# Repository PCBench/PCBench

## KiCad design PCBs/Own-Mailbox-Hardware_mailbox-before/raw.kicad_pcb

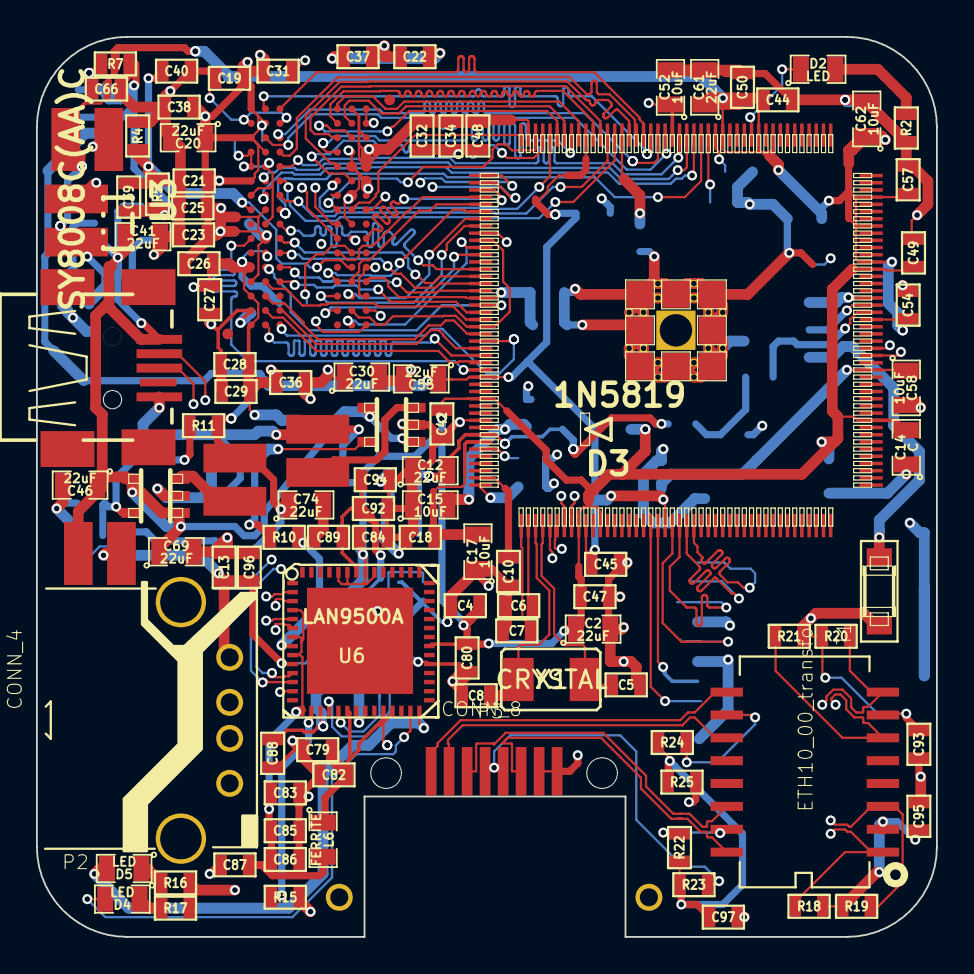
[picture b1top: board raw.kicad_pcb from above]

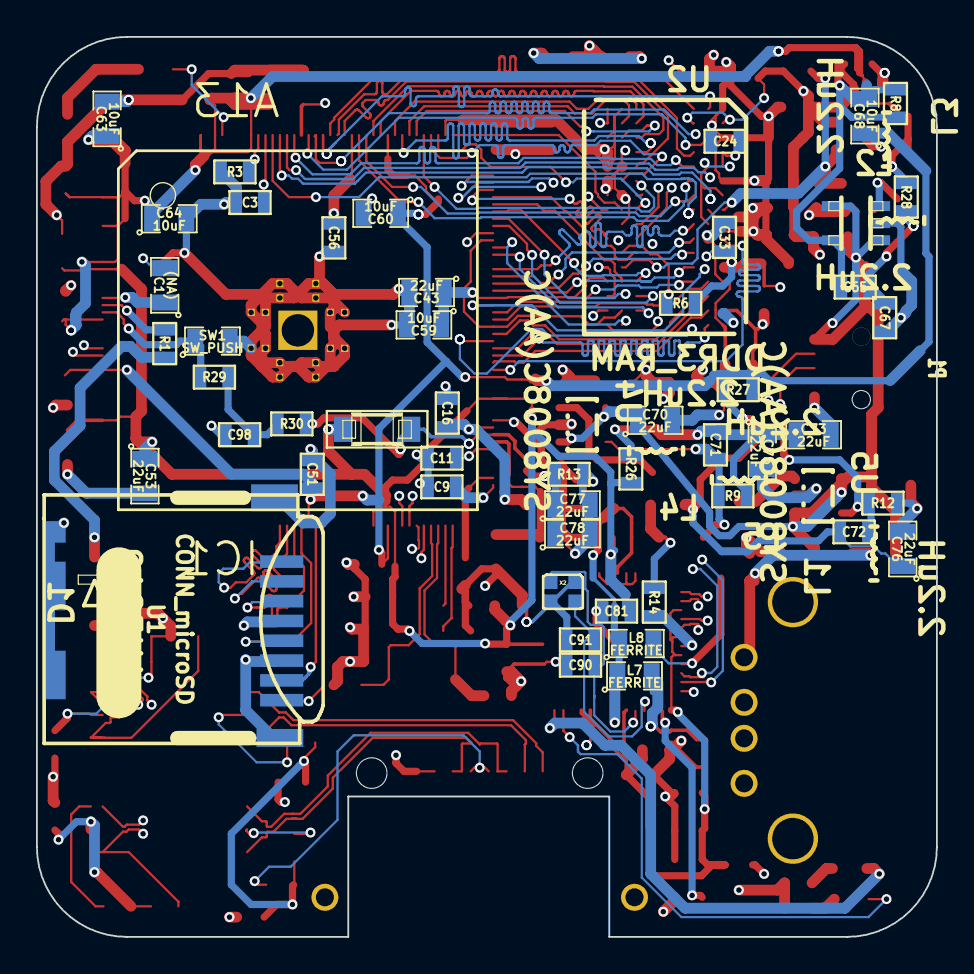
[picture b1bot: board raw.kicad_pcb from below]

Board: 4 copper layers, 50.0 x 50.0 mm, 154 parts (50 on the bottom side), 74 nets.

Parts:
C1: (NA); SM0805
C2, C12, C20, C30, C41, C43, C46, C53, C55, C61, C69, C70, C73, C74, C75, C76, C77, C78: 22uF; SM0805
C3, C4, C13, C16, C18, C19, C21, C23, C24, C25, C26, C27, C28, C29, C31, C32, C33, C34, C36, C37, C38, C39, C40, C42, C44, C45, C47, C48, C49, C50, C51, C54, C56, C57, C79, C80, C81, C82, C83, C84, C85, C86, C87, C88, C92, C93, C94, C95, C96: 100nF; SM0603
C5, C8, C90, C91: 10pF; SM0603
C6, C7, C9, C10, C22, C98: 1nF; SM0603
C11, C89, C97: 1uF; SM0603
C14: C; SM0805
C15, C17, C52, C58, C59, C60, C62, C63, C64, C68: 10uF; SM0805
C65, C72: 22pF; SM0603
C66, C67: 22uF; SM0603
C71: 47pF; SM0603
D1, D3: 1N5819; SOD-123
D2, D4, D5: LED; SM0805
IC1: A13; TQFP176
L1, L2, L3, L4, L5: 2.2uH; CD32
L6, L7, L8: FERRITE; SM0805
P1: CONN_4; CONN_USB_MINI_PIERRE
P2: CONN_4; USB-A_TH
P3: CONN_8; RJ45_LP_RA_SMT
R1: 47k; SM0603
R2: 500R; SM0603
R3: 240R; SM0603
R4, R5: 1k(1%); SM0603
R6: 240R(1%); SM0603
R7: 2k(1%); SM0603
R8: 1.5k(1%); SM0603
R9: 100k(1%); SM0603
R10: 22k(1%); SM0603
R11: 4.99k(1%); SM0603
R12: 3.3k(1%); SM0603
R13: 2.2k; SM0603
R14, R15: R; SM0603
R16, R17: 100R; SM0603
R18, R19, R20, R21: 50R; SM0603
R22, R23, R24, R25: 75R; SM0603
R26, R27, R28: 0R; SM0603
R29: 6.8k(1%); SM0603
R30: 100k (1%); SM0603
SW1: SW_PUSH; SM0805
T1: ETH10_00_transfo; H1601CG
U1: CONN_microSD; Memory_Card_microSD_DM3CS-SF
U2: DDR3_RAM; FBGA96
U3, U4, U5: SY8008C(AA)C; SOT23-5
U6: LAN9500A; QFN48
X1: CRYSTAL; SMDXTAL24mhz
X2: CRYSTAL_SMD2; Xtal25Mhz

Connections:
1V5: C19.1, C20.1, C21.1, C23.1, C24.1, C25.1, C26.1, C27.1, C28.1, C29.1, C30.1, C31.1, C32.1, C33.1, C34.1, C36.1, C37.1, C38.1, C39.1, C43.1, C48.1, C52.1, C56.1, C59.1, IC1.23, IC1.30, IC1.43, IC1.53, IC1.62, R5.1, R27.1, U2.A1, U2.A8, U2.B2, U2.C1, U2.C9, U2.D2, U2.D9, U2.E9, U2.F1, U2.G7, U2.H2, U2.H9, U2.K2, U2.K8, U2.N1, U2.N9, U2.R1, U2.R9
3VA: C12.2, C77.1, C78.1, D3.2, IC1.81, R13.1, R30.1
+5V: C41.1, C46.1, C69.1, C70.1, L1.2, P1.1, U3.1, U3.4, U4.1, U4.4, U5.1, U5.4
/Erhernet/RX+: P3.7, T1.11
/Erhernet/RX-: P3.8, T1.9
/Erhernet/TX+: P3.3, T1.16
/Erhernet/TX-: P3.6, T1.14
LED1: D4.2, U6.27
LED2: D5.2, U6.28
unnamed: C1.1, IC1.159
unnamed: C3.1, IC1.18
unnamed: C6.2, IC1.90
unnamed: C7.2, IC1.89
unnamed: C9.2, IC1.88
unnamed: C10.2, IC1.87
unnamed: C11.2, IC1.83
unnamed: C13.1, L1.1, P2.1
unnamed: C15.2, C16.2, IC1.80
unnamed: C17.2, C18.2, IC1.82
unnamed: C22.2, IC1.86
unnamed: C39.2, C40.1, R4.1, R5.2, U2.H1, U2.M8
unnamed: C65.1, C66.1, C67.1, L2.2, R7.1, R28.2
unnamed: C71.1, C73.1, C75.1, L4.2, R9.1, R26.2
unnamed: C71.2, R9.2, R10.1, U4.5
unnamed: C72.1, C74.1, C76.1, L5.2, R11.1, R27.2
unnamed: C72.2, R11.2, R12.1, U5.5
unnamed: C90.2, U6.19, X2.3
unnamed: C91.2, U6.18, X2.1
unnamed: C97.2, R22.1, R23.1, R24.1, R25.1
unnamed: C98.1, R29.1, R30.2
unnamed: D1.2, R1.1
unnamed: D2.1, IC1.12
unnamed: D2.2, R2.1
unnamed: D4.1, R17.1
unnamed: D5.1, R16.1
unnamed: IC1.17, R3.1
unnamed: IC1.158, R1.2
unnamed: L2.1, U3.3
unnamed: L4.1, U4.3
unnamed: L5.1, U5.3
unnamed: P3.1, P3.2, R25.2
unnamed: P3.4, P3.5, R23.2
unnamed: R6.1, U2.L8
unnamed: R14.2, U6.8
unnamed: R15.2, U6.16
unnamed: R22.2, T1.15
unnamed: R24.2, T1.10
RPX_N: R20.1, T1.8, U6.5
RPX_P: R21.1, T1.6, U6.6
SDC0_CLK: IC1.110, U1.5
SDC0_CMD: IC1.111, U1.3
SDC0_D0: IC1.108, U1.7
SDC0_D1: IC1.107, U1.8
SDC0_D2: IC1.113, U1.1
SDC0_D3: IC1.112, U1.2
SVREF: C1.2, C2.2, C3.2, C4.1, C5.1, C6.1, C7.1, C8.1, C9.1, C10.1, C11.1, C12.1, C13.2, C14.1, C15.1, C16.1, C17.1, C18.1, C19.2, C20.2, C21.2, C22.1, C23.2, C24.2, C25.2, C26.2, C27.2, C28.2, C29.2, C30.2, C31.2, C32.2, C33.2, C34.2, C36.2, C37.2, C38.2, C40.2, C41.2, C42.2, C43.2, C44.2, C45.2, C46.2, C47.2, C48.2, C49.2, C50.2, C51.2, C52.2, C53.2, C54.2, C55.2, C56.2, C57.2, C58.2, C59.2, C60.2, C61.2, C62.2, C63.2, C64.2, C65.2, C66.2, C67.2, C68.2, C69.2, C70.2, C73.2, C74.2, C75.2, C76.2, C77.2, C78.2, C79.2, C80.2, C81.2, C82.2, C83.2, C84.2, C85.2, C86.2, C87.2, C88.2, C89.2, C90.1, C91.1, C92.2, C93.1, C94.2, C95.2, C96.2, C97.1, C98.2, IC1.79, IC1.177, P1.4, P2.4, R2.2, R3.2, R4.2, R6.2, R7.2, R8.1, R8.2, R10.2, R12.2, R13.2, R14.1, R15.1, SW1.2, U1.6, U1.9, U2.A9, U2.B1, U2.B3, U2.B9, U2.D1, U2.D8, U2.E1, U2.E2, U2.E8, U2.F9, U2.G1, U2.G8, U2.G9, U2.J2, U2.J8, U2.L2, U2.M1, U2.M9, U2.P1, U2.P9, U2.T1, U2.T9, U3.2, U3.5, U4.2, U5.2, U6.13, U6.33, X2.2, X2.4
TPX_N: R19.2, T1.3, U6.2
TPX_P: R18.2, T1.1, U6.3
UART1_RX: IC1.151, P1.3
UART1_TX: IC1.152, P1.2
UBOOT: IC1.157, R29.2, SW1.1
USB_ETH_N: IC1.93, U6.11
USB_ETH_P: IC1.94, U6.12
USB_HOST_N: IC1.95, P2.2
USB_HOST_P: IC1.96, P2.3
VCC: C2.1, C4.2, C14.2, C42.1, C47.1, C49.1, C53.1, C79.1, C80.1, C81.1, C82.1, C84.1, C93.2, C95.1, D1.1, D3.1, IC1.5, IC1.76, IC1.97, IC1.100, IC1.142, IC1.163, L6.1, R16.2, R17.2, R18.1, R19.1, R20.2, R21.2, R26.1, T1.2, T1.7, U1.4, U6.20, U6.24, U6.25, U6.35, U6.48, U6.49, U6.51, U6.52
VDD33A: C83.1, C85.1, C86.1, C87.1, L6.2, U6.4, U6.7, U6.9, U6.15
VDDBUSPLL: C88.1, L7.2, U6.17
VDDCORE: C89.1, C92.1, C94.1, L7.1, L8.1, U6.21, U6.50
VDDPLL: C96.1, L8.2, U6.10
VDD_CPU: C44.1, C50.1, C54.1, C57.1, C61.1, C62.1, C63.1, C64.1, IC1.4, IC1.9, IC1.11, IC1.16, IC1.156, IC1.164, IC1.169, IC1.173, L3.1, R28.1
VDD_INT: C45.1, C51.1, C55.1, C58.1, C60.1, C68.1, IC1.35, IC1.73, IC1.98, IC1.109, IC1.149, L3.2
X1_N: C5.2, IC1.92, X1.1
X1_P: C8.2, IC1.91, X1.2

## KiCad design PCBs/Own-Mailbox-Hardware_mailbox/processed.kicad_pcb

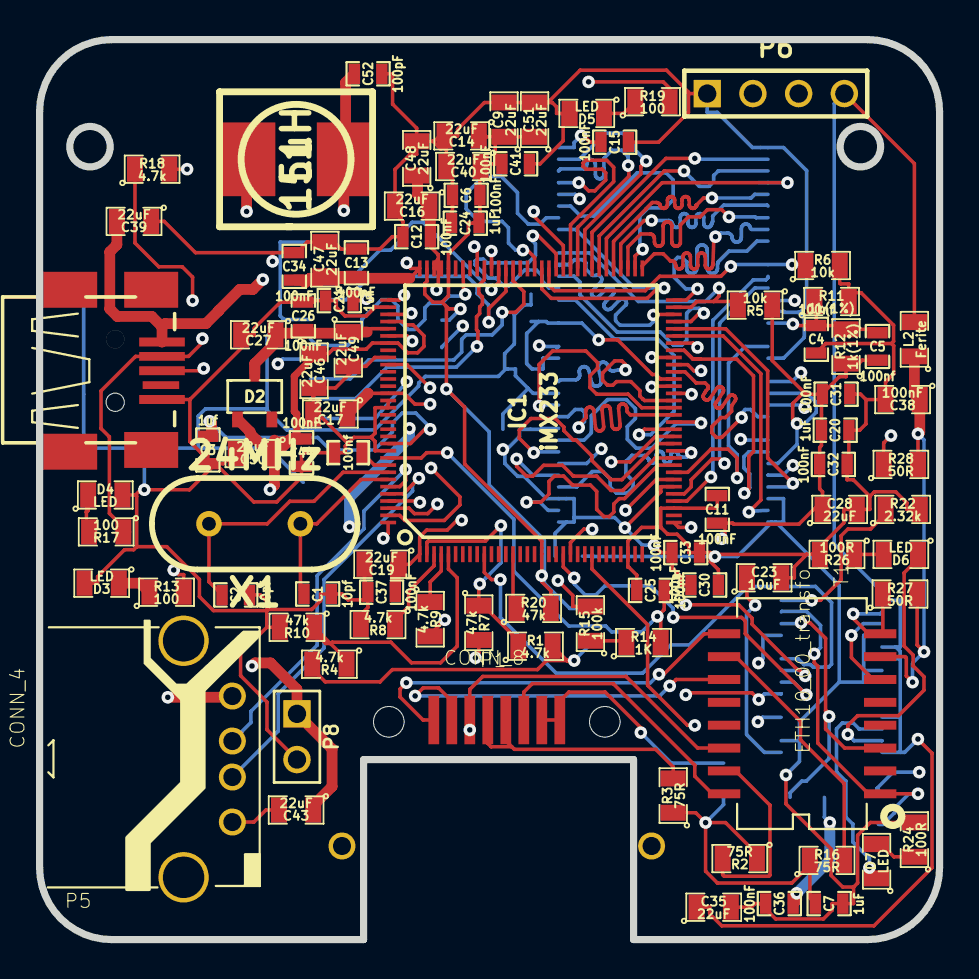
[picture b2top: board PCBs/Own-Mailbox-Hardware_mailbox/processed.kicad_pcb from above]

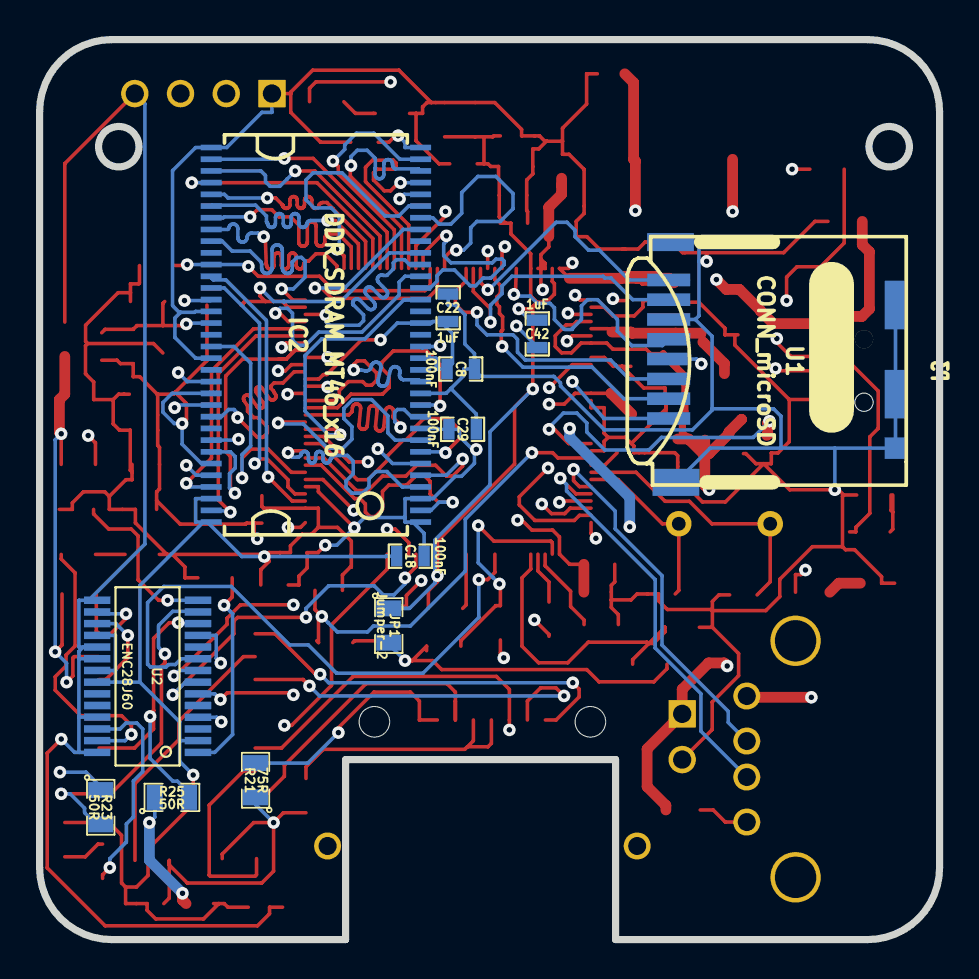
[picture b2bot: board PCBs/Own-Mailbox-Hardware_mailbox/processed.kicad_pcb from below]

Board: 4 copper layers, 50.0 x 50.0 mm, 99 parts (12 on the bottom side), 107 nets.

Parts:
C1, C2: 10pf; SM0603_Capa
C3: 1uf; SM0603_Capa
C4, C5: 100nf; SM0603_Capa
C6, C8, C11, C12, C13, C15, C18, C25, C26, C29, C30, C31, C32, C33, C34, C36, C37, C41, C44: 100nF; SM0603_Capa
C7, C20, C21, C22, C24, C42: 1uF; SM0603_Capa
C9, C14, C16, C17, C19, C27, C28, C35, C39, C40, C43, C46, C47, C48, C49, C50, C51: 22uF; SM0805
C10: 100nf; SM0603_Opendous
C23: 10uF; SM0805
C38: 100nF; SM0805
C52: 100pF; SM0603_Capa
D2: D_schottky; SOT23-3_Opendous
D3, D4, D5, D6, D7: LED; SM0805
IC1: iMX233; LQFP128_14x14mm_0.4mmPitch_iMX233
IC2: DDR_SDRAM_MT46_x16; TSOP66_JEDEC_DDR_SDRAM
JP1: Jumper-2; SM0805
L1: 15uH; inductor22
L2: Ferite; SM0805
P1: CONN_8; RJ45_LP_RA_SMT
P3: CONN_4; CONN_USB_MINI_PIERRE
P5: CONN_4; USB-A_TH
P6: CONN_4; PIN_ARRAY_4x1
P8: CONN_2; PIN_ARRAY_2X1
R1, R4, R8, R9, R18: 4.7k; SM0805
R2, R3, R16, R21: 75R; SM0805
R5, R6: 10k; SM0805
R7, R10, R20: 47k; SM0805
R11, R12: 1k(1%); SM0805
R13, R17, R19: 100; SM0805
R14: 1K; SM0805
R15: 100k; SM0805
R22: 2.32k; SM0805
R23, R25, R27, R28: 50R; SM0805
R24, R26: 100R; SM0805
T1: ETH10_00_transfo; H1601CG
U1: CONN_microSD; Memory_Card_microSD_DM3CS-SF
U2: ENC28J60; tssop-28
X1: 24MHz; HC-49V

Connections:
5VOUT: C21.1, C39.2, IC1.102, P3.1, P5.1
+2.5V: C5.1, C8.1, C11.1, C15.1, C18.1, C20.1, C22.1, C28.1, C29.1, C30.1, C31.1, C32.1, C33.1, IC1.38, IC1.45, IC1.53, IC1.106, IC2.1, IC2.3, IC2.9, IC2.15, IC2.18, IC2.33, IC2.55, IC2.61, R5.1, R12.1
+3.3V: C6.1, C9.1, C14.1, C24.1, C35.1, C40.1, C41.1, C42.1, C51.1, IC1.18, IC1.92, IC1.95, JP1.1, L2.2, P6.4, R13.2, R18.2, R20.2, U1.4, U2.15, U2.19, U2.20, U2.25, U2.28
/Ethernet/RX+: P1.7, T1.11
/Ethernet/RX-: P1.8, T1.9
/Ethernet/TX+: P1.3, T1.16
/Ethernet/TX-: P1.6, T1.14
/LCD_D0: IC1.2, R1.1, R7.1
/LCD_D1: IC1.3, R8.1
/LCD_D2: IC1.4, R9.1
/LCD_D3: IC1.5, R4.1, R10.1
/LCD_RS: IC1.14, R20.1
/SD_CLOCK: IC1.90, U1.5
/SD_CMD: IC1.83, U1.3
/UART2_RX: IC1.128, P6.3
/UART2_TX: IC1.127, P6.2
/U_RX: IC1.125, P3.3, R18.1
/U_TX: IC1.126, P3.2, R17.1
DDRA0: IC1.76, IC2.29
DDRA1: IC1.75, IC2.30
DDRA2: IC1.74, IC2.31
DDRA3: IC1.73, IC2.32
DDRA4: IC1.72, IC2.35
DDRA5: IC1.71, IC2.36
DDRA6: IC1.70, IC2.37
DDRA7: IC1.69, IC2.38
DDRA8: IC1.68, IC2.39
DDRA9: IC1.67, IC2.40
DDRA10: IC1.66, IC2.28
DDRA11: IC1.65, IC2.41
DDRA12: IC1.64, IC2.42
DDR_BA0: IC1.79, IC2.26
DDR_BA1: IC1.80, IC2.27
DDR_CAS: IC1.61, IC2.22
DDR_CE0n: IC1.63, IC2.24, R5.2
DDR_CKE: IC1.78, IC2.44, R6.1
DDR_CLK: IC1.36, IC2.45
DDR_CLKn: IC1.37, IC2.46
DDR_DO0: IC1.41, IC2.2
DDR_DO1: IC1.43, IC2.4
DDR_DO2: IC1.42, IC2.5
DDR_DO3: IC1.44, IC2.7
DDR_DO4: IC1.47, IC2.8
DDR_DO5: IC1.48, IC2.10
DDR_DO6: IC1.49, IC2.11
DDR_DO7: IC1.50, IC2.13
DDR_DO8: IC1.51, IC2.54
DDR_DO9: IC1.52, IC2.56
DDR_DO10: IC1.54, IC2.57
DDR_DO11: IC1.55, IC2.59
DDR_DO12: IC1.57, IC2.60
DDR_DO13: IC1.58, IC2.62
DDR_DO14: IC1.60, IC2.63
DDR_DO15: IC1.59, IC2.65
DDR_DQM0: IC1.46, IC2.20
DDR_DQM1: IC1.56, IC2.47
DDR_DQS0: IC1.39, IC2.16
DDR_DQS1: IC1.40, IC2.51
DDR_RAS: IC1.62, IC2.23
DDR_WEn: IC1.77, IC2.21
GND: C1.1, C2.1, C3.2, C4.2, C6.2, C7.1, C8.2, C9.2, C10.2, C11.2, C12.2, C13.2, C14.2, C15.2, C16.2, C17.2, C18.2, C19.2, C20.2, C21.2, C22.2, C23.2, C24.2, C25.2, C26.2, C27.2, C28.2, C29.2, C30.2, C31.2, C32.2, C33.2, C34.2, C35.2, C36.1, C37.2, C38.2, C39.1, C40.2, C41.2, C42.2, C43.2, C44.2, C46.2, C47.2, C48.2, C49.2, C50.2, C51.2, C52.1, D3.2, D4.2, D5.2, IC1.30, IC1.35, IC1.98, IC1.105, IC1.111, IC1.112, IC1.118, IC2.6, IC2.12, IC2.34, IC2.48, IC2.52, IC2.64, IC2.66, P3.4, P5.4, P6.1, P8.2, R6.2, R7.2, R8.2, R9.2, R10.2, R11.2, R15.2, R22.2, R24.2, R26.2, U1.6, U1.9, U2.2, U2.11, U2.18, U2.21, U2.22
unnamed: C3.1, IC1.117
unnamed: C4.1, C5.2, IC2.49, R11.1, R12.2
unnamed: C7.2, R2.1, R3.1, R16.1, R21.1
unnamed: C23.1, U2.1
unnamed: C36.2, R23.1, R25.1
unnamed: C38.1, L2.1, R27.2, R28.2, T1.7
unnamed: C52.2, IC1.99, L1.2
unnamed: D3.1, R13.1
unnamed: D4.1, R17.2
unnamed: D5.1, R19.1
unnamed: D6.1, U2.27
unnamed: D6.2, R26.1
unnamed: D7.1, U2.26
unnamed: D7.2, R24.1
unnamed: IC1.84, U1.7
unnamed: IC1.85, U1.8
unnamed: IC1.86, U1.1
unnamed: IC1.87, U1.2
unnamed: IC1.88, R19.2
unnamed: IC1.97, L1.1
unnamed: IC1.123, P5.2
unnamed: IC1.124, P5.3
unnamed: JP1.2, R1.2, R4.2
unnamed: P1.1, P1.2, R21.2
unnamed: P1.4, P1.5, R3.2
unnamed: R2.2, T1.15
unnamed: R14.1, R15.1
unnamed: R16.2, T1.10
unnamed: R22.1, U2.14
unnamed: R23.2, T1.1, U2.13
unnamed: R25.2, T1.3, U2.12
unnamed: R27.1, T1.8, U2.16
unnamed: R28.1, T1.6, U2.17
PSWITCH: C25.1, IC1.119, R14.2
SPI_CS: IC1.10, U2.9
SPI_INT: IC1.25, U2.4
SPI_MISO: IC1.22, U2.6
SPI_MOSI: IC1.21, U2.7
SPI_SCK: IC1.33, U2.8
VDD4P2: C26.1, C27.1, C49.1, D2.2, IC1.101
VDDA: C13.1, C17.1, C34.1, C47.1, IC1.96, IC1.110
VDDD: C12.1, C16.1, C19.1, C37.1, C48.1, IC1.1, IC1.93, IC1.94
VDD_BATT: C43.1, C44.1, C46.1, C50.1, D2.1, IC1.100, IC1.103, P8.1
VDD_XTAL: C10.1, IC1.120
XTALI: C1.2, IC1.122, X1.1
XTALO: C2.2, IC1.121, X1.2

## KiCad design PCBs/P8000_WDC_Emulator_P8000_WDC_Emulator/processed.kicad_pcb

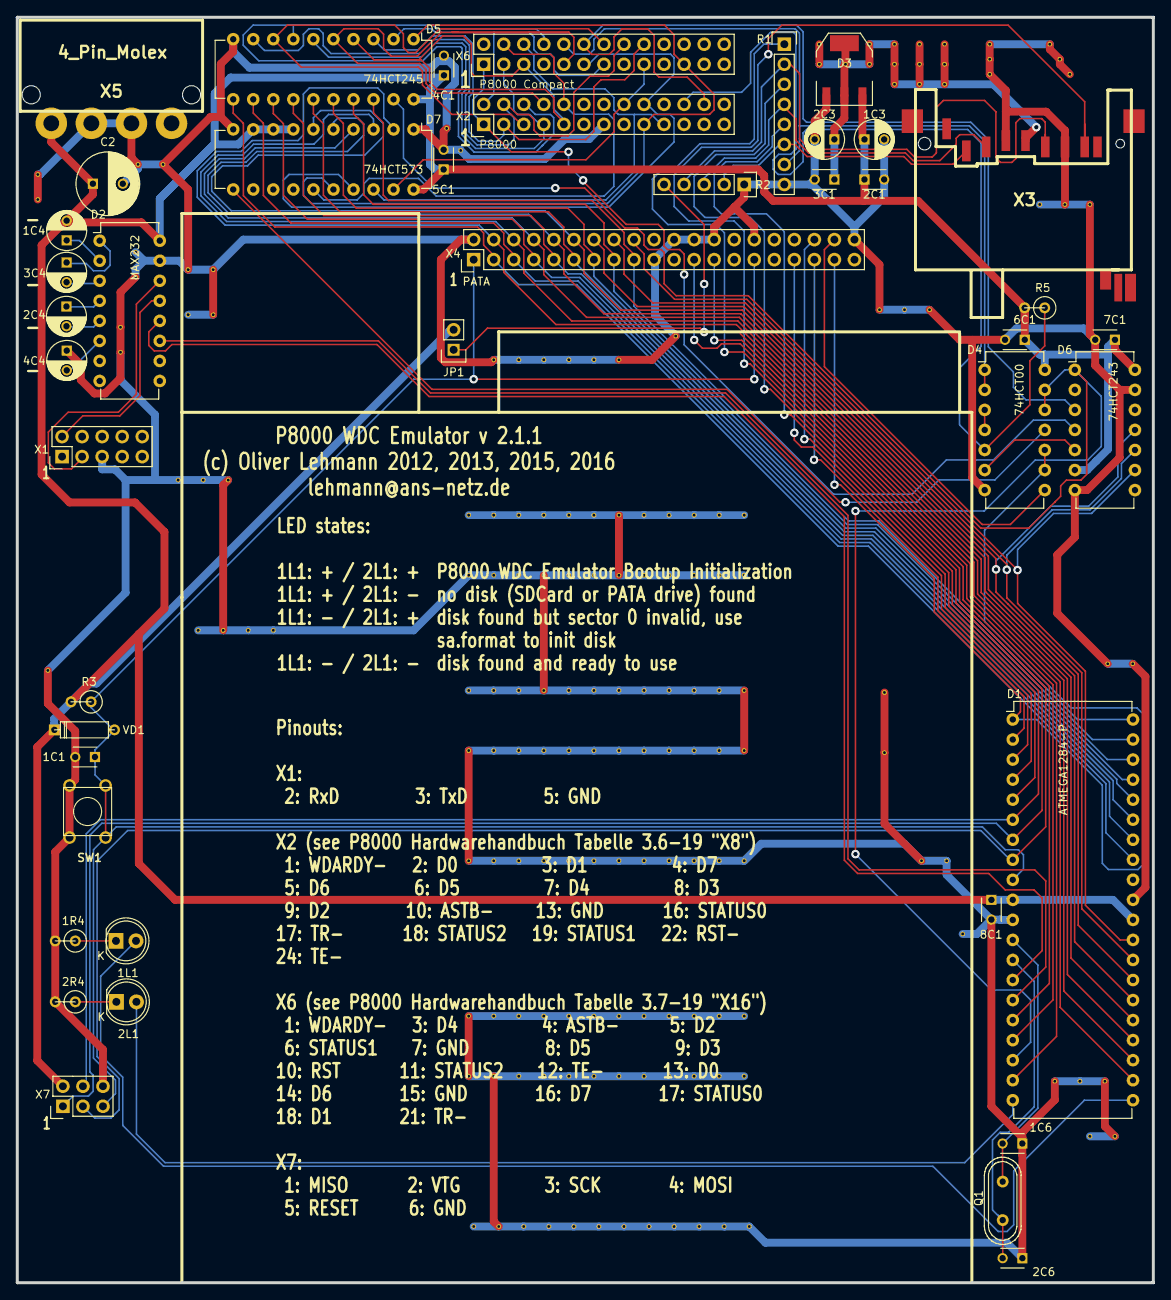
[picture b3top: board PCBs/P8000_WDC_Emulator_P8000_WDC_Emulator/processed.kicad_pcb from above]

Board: 2 copper layers, 144.0 x 160.4 mm, 214 parts (0 on the bottom side), 72 nets.

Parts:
1C1, 2C1, 3C1, 4C1, 5C1, 6C1, 7C1, 8C1: 100n; C_Disc_D3_P2.5
1C3, 2C3: 100u; C_Radial_D5_L6_P2.5
1C4, 2C4, 3C4, 4C4: 1u; C_Radial_D5_L6_P2.5
1C6, 2C6: 22p; C_Disc_D3_P2.5
1L1, 2L1: LED; LED-5MM
1R4, 2R4: 300; R1
C2: 470u; C_Radial_D8_L13_P3.8
D1: ATMEGA1284-P; DIP-40_W15.24mm
D2: MAX232; DIP-16_W7.62mm
D3: TS1117 BCW33; SOT-223
D4: 74HCT00; DIP-14_W7.62mm
D5: 74HCT245; DIP-20_W7.62mm
D6: 74HCT243; DIP-14_W7.62mm
D7: 74HCT573; DIP-20_W7.62mm
Hole-Inner-1, Hole-Inner-2, Hole-Inner-3, Hole-Inner-4: VAL**; HOLE_4x8mm_4mmclear_pad
Hole-Outer-1, Hole-Outer-2, Hole-Outer-3, Hole-Outer-4: VAL**; HOLE_4x8mm_pad
JP1: JUMPER; Pin_Header_Straight_1x02
Q1: CRYSTAL; Crystal_HC49-U_Vertical
R1: 1k8; Pin_Header_Straight_1x08
R2: 3k3; Pin_Header_Straight_1x05
R3: 10k; R1
R5: 4k7; R1
SW1: SW_PUSH; SW_6x6
VD1: 1N4148; D3
VIA-0.6mm, VIA-0.6mm_2, VIA-0.6mm_3, VIA-0.6mm_4, VIA-0.6mm_5, VIA-0.6mm_6, VIA-0.6mm_7, VIA-0.6mm_8, VIA-0.6mm_9, VIA-0.6mm_10, VIA-0.6mm_11, VIA-0.6mm_12, VIA-0.6mm_13, VIA-0.6mm_14, VIA-0.6mm_15, VIA-0.6mm_16, VIA-0.6mm_17, VIA-0.6mm_18, VIA-0.6mm_19, VIA-0.6mm_20, VIA-0.6mm_21, VIA-0.6mm_22, VIA-0.6mm_23, VIA-0.6mm_24, VIA-0.6mm_25, VIA-0.6mm_26, VIA-0.6mm_27, VIA-0.6mm_28, VIA-0.6mm_29, VIA-0.6mm_30, VIA-0.6mm_31, VIA-0.6mm_32, VIA-0.6mm_33, VIA-0.6mm_34, VIA-0.6mm_35, VIA-0.6mm_36, VIA-0.6mm_37, VIA-0.6mm_38, VIA-0.6mm_39, VIA-0.6mm_40, VIA-0.6mm_41, VIA-0.6mm_42, VIA-0.6mm_43, VIA-0.6mm_44, VIA-0.6mm_45, VIA-0.6mm_46, VIA-0.6mm_47, VIA-0.6mm_48, VIA-0.6mm_49, VIA-0.6mm_50, VIA-0.6mm_51, VIA-0.6mm_52, VIA-0.6mm_53, VIA-0.6mm_54, VIA-0.6mm_55, VIA-0.6mm_56, VIA-0.6mm_57, VIA-0.6mm_58, VIA-0.6mm_59, VIA-0.6mm_60, VIA-0.6mm_61, VIA-0.6mm_62, VIA-0.6mm_63, VIA-0.6mm_64, VIA-0.6mm_65, VIA-0.6mm_66, VIA-0.6mm_67, VIA-0.6mm_68, VIA-0.6mm_69, VIA-0.6mm_70, VIA-0.6mm_71, VIA-0.6mm_72, VIA-0.6mm_73, VIA-0.6mm_74, VIA-0.6mm_75, VIA-0.6mm_76, VIA-0.6mm_77, VIA-0.6mm_78, VIA-0.6mm_79, VIA-0.6mm_80, VIA-0.6mm_81, VIA-0.6mm_82, VIA-0.6mm_83, VIA-0.6mm_84, VIA-0.6mm_85, VIA-0.6mm_86, VIA-0.6mm_87, VIA-0.6mm_88, VIA-0.6mm_89, VIA-0.6mm_90, VIA-0.6mm_91, VIA-0.6mm_92, VIA-0.6mm_93, VIA-0.6mm_94, VIA-0.6mm_95, VIA-0.6mm_96, VIA-0.6mm_97, VIA-0.6mm_98, VIA-0.6mm_99, VIA-0.6mm_100, VIA-0.6mm_101, VIA-0.6mm_102, VIA-0.6mm_103, VIA-0.6mm_104, VIA-0.6mm_105, VIA-0.6mm_106, VIA-0.6mm_107, VIA-0.6mm_108, VIA-0.6mm_109, VIA-0.6mm_110, VIA-0.6mm_111, VIA-0.6mm_112, VIA-0.6mm_113, VIA-0.6mm_114, VIA-0.6mm_115, VIA-0.6mm_116, VIA-0.6mm_117, VIA-0.6mm_118, VIA-0.6mm_119, VIA-0.6mm_120, VIA-0.6mm_121, VIA-0.6mm_122, VIA-0.6mm_123, VIA-0.6mm_124, VIA-0.6mm_125, VIA-0.6mm_126, VIA-0.6mm_127, VIA-0.6mm_128, VIA-0.6mm_129, VIA-0.6mm_130, VIA-0.6mm_131, VIA-0.6mm_132, VIA-0.6mm_133, VIA-0.6mm_134, VIA-0.6mm_135, VIA-0.6mm_136, VIA-0.6mm_137, VIA-0.6mm_138, VIA-0.6mm_139, VIA-0.6mm_140, VIA-0.6mm_141, VIA-0.6mm_142, VIA-0.6mm_143, VIA-0.6mm_144, VIA-0.6mm_145, VIA-0.6mm_146, VIA-0.6mm_147, VIA-0.6mm_148, VIA-0.6mm_149, VIA-0.6mm_150, VIA-0.6mm_151, VIA-0.6mm_152, VIA-0.6mm_153, VIA-0.6mm_154, VIA-0.6mm_155, VIA-0.6mm_156, VIA-0.6mm_157, VIA-0.6mm_158, VIA-0.6mm_159, VIA-0.6mm_160, VIA-0.6mm_161, VIA-0.6mm_162, VIA-0.6mm_163: VAL**; VIA-0.6mm
X1: RS-232; Pin_Header_Straight_2x05
X2: P8000; Pin_Header_Straight_2x13
X3: SD-CON; sd_cocket_yamaichi_fps009_3001
X4: PATA; Pin_Header_Straight_2x20
X5: 4_Pin_Molex; 4PIN_MOLEX
X6: P8000-Compact; Pin_Header_Straight_2x13
X7: AVR-ISP-6; Pin_Header_Straight_2x03

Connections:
+3V3: 2C3.1, 3C1.1, D3.2, VIA-0.6mm_117.1, VIA-0.6mm_118.1, VIA-0.6mm_119.1, VIA-0.6mm_120.1, VIA-0.6mm_121.1, VIA-0.6mm_122.1, VIA-0.6mm_123.1, VIA-0.6mm_124.1, VIA-0.6mm_125.1, VIA-0.6mm_126.1, VIA-0.6mm_127.1, VIA-0.6mm_128.1, VIA-0.6mm_129.1, VIA-0.6mm_130.1, X3.4
//ASTB: D7.15, X2.10, X6.4
//CS0: D1.1, D4.9, D4.10, X4.37
//RD: D1.17, X4.25
//RDY: D6.4, X2.1, X6.1
//RST2: D4.5, R5.1, X2.22
//TE: D6.3, X2.24, X6.12
//TR: D5.1, D7.16, X2.17, X6.21
//WR: D1.16, X4.23
/D0: D5.2, X2.2, X6.13
/D1: D5.3, X2.3, X6.18
/D2: D5.4, X2.9, X6.5
/D3: D5.5, X2.8, X6.9
/D4: D5.6, X2.7, X6.3
/D5: D5.7, X2.6, X6.8
/D6: D5.8, X2.5, X6.14
/D7: D5.9, X2.4, X6.16
/DA0: D1.2, X4.35
/DA1: D1.3, X4.33
/DA2: D1.4, X4.36
/PA0: D1.40, D5.18, X4.17
/PA1: D1.39, D5.17, X4.15
/PA2: D1.38, D5.16, X4.13
/PA3: D1.37, D5.15, X4.11
/PA4: D1.36, D5.14, X4.9
/PA5: D1.35, D5.13, X4.7
/PA6: D1.34, D5.12, X4.5
/PA7: D1.33, D5.11, X4.3
/PC0: D1.22, D7.2, X4.4
/PC1: D1.23, D7.3, X4.6
/PC2: D1.24, D7.4, X4.8
/PC3: D1.25, D7.5, X4.10
/PC4: D1.26, D7.6, X4.12
/PC5: D1.27, D6.11, X4.14
/PC6: D1.28, D6.10, X4.16
/PC7: D1.29, D6.9, X4.18
/RST: D4.6, D6.5
/RST1: D4.1, D4.2, R1.7, X6.10
/STATUS0: D7.19, X2.16, X6.17
/STATUS1: D7.18, X2.19, X6.6
/STATUS2: D7.17, X2.18, X6.11
GND: 1C1.2, 1C3.2, 1C6.1, 1R4.2, 2C1.2, 2C3.2, 2C6.1, 2R4.2, 3C1.2, 4C1.2, 4C4.1, 5C1.2, 6C1.2, 7C1.2, 8C1.2, C2.2, D1.11, D1.31, D2.15, D3.1, D4.7, D5.10, D6.7, D6.13, D7.1, D7.10, R1.8, R2.1, SW1.2, VIA-0.6mm.1, VIA-0.6mm_2.1, VIA-0.6mm_3.1, VIA-0.6mm_4.1, VIA-0.6mm_5.1, VIA-0.6mm_6.1, VIA-0.6mm_7.1, VIA-0.6mm_8.1, VIA-0.6mm_9.1, VIA-0.6mm_10.1, VIA-0.6mm_11.1, VIA-0.6mm_12.1, VIA-0.6mm_13.1, VIA-0.6mm_14.1, VIA-0.6mm_15.1, VIA-0.6mm_16.1, VIA-0.6mm_17.1, VIA-0.6mm_18.1, VIA-0.6mm_19.1, VIA-0.6mm_20.1, VIA-0.6mm_21.1, VIA-0.6mm_22.1, VIA-0.6mm_23.1, VIA-0.6mm_24.1, VIA-0.6mm_25.1, VIA-0.6mm_26.1, VIA-0.6mm_27.1, VIA-0.6mm_28.1, VIA-0.6mm_29.1, VIA-0.6mm_30.1, VIA-0.6mm_31.1, VIA-0.6mm_32.1, VIA-0.6mm_33.1, VIA-0.6mm_34.1, VIA-0.6mm_35.1, VIA-0.6mm_36.1, VIA-0.6mm_37.1, VIA-0.6mm_38.1, VIA-0.6mm_39.1, VIA-0.6mm_40.1, VIA-0.6mm_41.1, VIA-0.6mm_42.1, VIA-0.6mm_43.1, VIA-0.6mm_44.1, VIA-0.6mm_45.1, VIA-0.6mm_46.1, VIA-0.6mm_47.1, VIA-0.6mm_48.1, VIA-0.6mm_49.1, VIA-0.6mm_50.1, VIA-0.6mm_51.1, VIA-0.6mm_52.1, VIA-0.6mm_53.1, VIA-0.6mm_54.1, VIA-0.6mm_55.1, VIA-0.6mm_56.1, VIA-0.6mm_57.1, VIA-0.6mm_58.1, VIA-0.6mm_59.1, VIA-0.6mm_60.1, VIA-0.6mm_61.1, VIA-0.6mm_62.1, VIA-0.6mm_63.1, VIA-0.6mm_64.1, VIA-0.6mm_65.1, VIA-0.6mm_66.1, VIA-0.6mm_67.1, VIA-0.6mm_68.1, VIA-0.6mm_69.1, VIA-0.6mm_70.1, VIA-0.6mm_71.1, VIA-0.6mm_72.1, VIA-0.6mm_73.1, VIA-0.6mm_74.1, VIA-0.6mm_75.1, VIA-0.6mm_76.1, VIA-0.6mm_77.1, VIA-0.6mm_78.1, VIA-0.6mm_79.1, VIA-0.6mm_80.1, VIA-0.6mm_81.1, VIA-0.6mm_82.1, VIA-0.6mm_83.1, VIA-0.6mm_84.1, VIA-0.6mm_85.1, VIA-0.6mm_86.1, VIA-0.6mm_87.1, VIA-0.6mm_88.1, VIA-0.6mm_89.1, VIA-0.6mm_90.1, VIA-0.6mm_91.1, VIA-0.6mm_92.1, VIA-0.6mm_93.1, VIA-0.6mm_94.1, VIA-0.6mm_95.1, VIA-0.6mm_96.1, VIA-0.6mm_97.1, VIA-0.6mm_98.1, VIA-0.6mm_99.1, VIA-0.6mm_100.1, VIA-0.6mm_101.1, VIA-0.6mm_102.1, VIA-0.6mm_103.1, VIA-0.6mm_104.1, VIA-0.6mm_105.1, VIA-0.6mm_106.1, VIA-0.6mm_107.1, VIA-0.6mm_108.1, VIA-0.6mm_109.1, VIA-0.6mm_110.1, VIA-0.6mm_111.1, VIA-0.6mm_112.1, VIA-0.6mm_113.1, VIA-0.6mm_114.1, VIA-0.6mm_115.1, VIA-0.6mm_116.1, VIA-0.6mm_131.1, VIA-0.6mm_132.1, VIA-0.6mm_133.1, VIA-0.6mm_134.1, VIA-0.6mm_135.1, VIA-0.6mm_136.1, VIA-0.6mm_137.1, VIA-0.6mm_138.1, VIA-0.6mm_139.1, VIA-0.6mm_140.1, VIA-0.6mm_141.1, VIA-0.6mm_142.1, VIA-0.6mm_143.1, VIA-0.6mm_144.1, VIA-0.6mm_145.1, VIA-0.6mm_146.1, VIA-0.6mm_147.1, VIA-0.6mm_148.1, VIA-0.6mm_149.1, VIA-0.6mm_150.1, VIA-0.6mm_151.1, VIA-0.6mm_152.1, VIA-0.6mm_153.1, VIA-0.6mm_154.1, VIA-0.6mm_155.1, VIA-0.6mm_156.1, VIA-0.6mm_157.1, VIA-0.6mm_158.1, VIA-0.6mm_159.1, VIA-0.6mm_160.1, VIA-0.6mm_161.1, VIA-0.6mm_162.1, VIA-0.6mm_163.1, X1.5, X2.13, X3.3, X3.6, X4.2, X4.19, X4.22, X4.24, X4.26, X4.30, X4.40, X5.2, X5.3, X7.6
unnamed: 1C1.1, D1.9, R3.1, SW1.1, VD1.2, X4.1, X4.29, X7.5
unnamed: 1C4.1, D2.2
unnamed: 1C6.2, D1.12, Q1.2
unnamed: 1L1.1, 1R4.1
unnamed: 1L1.2, D1.21
unnamed: 2C4.1, D2.4
unnamed: 2C4.2, D2.5
unnamed: 2C6.2, D1.13, Q1.1
unnamed: 2L1.1, 2R4.1
unnamed: 2L1.2, D1.20
unnamed: 3C4.1, D2.1
unnamed: 3C4.2, D2.3
unnamed: 4C4.2, D2.6
unnamed: D1.5, R1.5
unnamed: D1.6, R1.3, X7.4
unnamed: D1.7, X3.7, X7.1
unnamed: D1.8, R1.1, X7.3
unnamed: D1.14, D2.12
unnamed: D1.15, D2.11
unnamed: D1.18, D4.12, D4.13, D5.19, D6.1
unnamed: D1.19, JP1.1, R2.5
unnamed: D2.13, X1.2
unnamed: D2.14, X1.3
unnamed: D4.3, D4.4
unnamed: D4.8, X4.38
unnamed: D4.11, D7.11
unnamed: R1.2, R2.4, X3.5
unnamed: R1.4, R2.3, X3.2
unnamed: R1.6, R2.2, X3.1
VCC: 1C3.1, 1C4.2, 2C1.1, 4C1.1, 5C1.1, 6C1.1, 7C1.1, 8C1.1, C2.1, D1.10, D1.30, D2.16, D3.3, D4.14, D5.20, D6.6, D6.14, D7.7, D7.8, D7.9, D7.20, JP1.2, R3.2, R5.2, VD1.1, X5.1, X7.2

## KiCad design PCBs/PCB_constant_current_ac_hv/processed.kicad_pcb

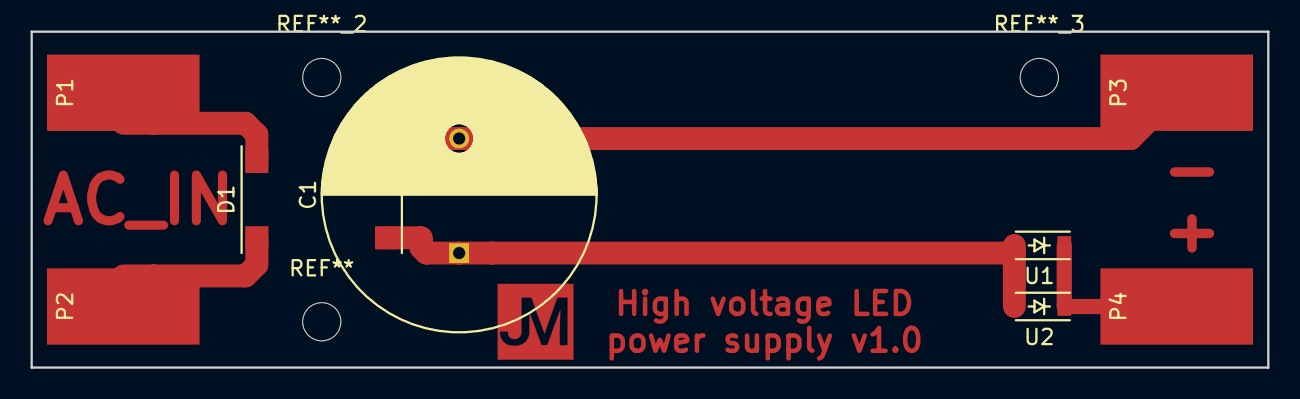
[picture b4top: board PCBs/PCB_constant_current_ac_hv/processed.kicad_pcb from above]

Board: 2 copper layers, 81.0 x 22.0 mm, 8 parts (0 on the bottom side), 5 nets.

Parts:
C1: 120uF@400V; C_Radial_D18_L36_P7.5
D1: DB207S
P1, P2, P3, P4: CONN_01X01; SolderWirePad_single_SMD_5x10mm
U1, U2: NSI45030AT1G; SOD-123

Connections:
/AC_IN1: D1.2, P1.1
/AC_IN2: D1.4, P2.1
/NEG_OUT: C1.2, D1.1, P3.1
/POS_OUT: P4.1, U1.1, U2.1
unnamed: C1.1, D1.3, U1.2, U2.2

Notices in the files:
PCBs/Own-Mailbox-Hardware_mailbox/processed.kicad_pcb:
CopyRight Pierre Parent & Ael gain
this is open hardware you may redistribute it under the cern open harware  license 1.3
parts and their libraries:
Copyright © 2012, Michel Stempin, All rights reserved
Licenced under Creative Commons CC BY-SA 3.0 license.
